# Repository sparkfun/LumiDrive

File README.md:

SparkFun LumiDrive LED Driver 
========================================

[*SparkFun LumiDrive LED Driver (14779)*](https://www.sparkfun.com/products/14779)

The LumiDrive LED Driver is SparkFun’s foray into all things Python on micro-controllers. With the SparkFun LumiDrive you will be able to control and personalize a whole strand of APA102s directly from the board itself. We’ve broken out a number of analog and digital pins from the on board SAMD21G-AU microcontroller to incorporate your own external buttons, switches, and other interfaces to interact with your addressable LED strip.

It feels like Arduino, but without the need to upload and compile code. Because the LumiDrive opens up like a USB drive on your computer when you plug it in and the code you write lives directly inside the drive it feels very much like an Arduino-device. The fact that you don’t need to upload and compile code makes it a great transitionary LED driver from your traditional Arduino!

The SparkFun LumiDrive has been equipped with a USB-C connector which is capable enough to supply up to 1.5 Amps from a 3.1 USB port, a LiPo connector and charge circuit for portable power, as well as two poke-home connectors to allow you to plug in wires without the need for solder.

Repository Contents
-------------------

* **/Buzzard Labels** - Silkscreen Libraries for Eagle Files
* **/Hardware** - Eagle design files (.brd, .sch)

Documentation
--------------
* **[Hookup Guide](https://learn.sparkfun.com/tutorials/lumidrive-hookup-guide)** - Basic hookup guide for the LumiDrive LED Driver.
* **[Example Code](https://github.com/sparkfun/SparkFun_LumiDrive_Example_Code)** - Example Code for the LumiDrive LED Driver.

License Information
-------------------

This product is _**open source**_! 

Please review the LICENSE.md file for license information. 

If you have any questions or concerns on licensing, please contact techsupport@sparkfun.com.

Distributed as-is; no warranty is given.

- Your friends at SparkFun.

_<COLLABORATION CREDIT>_

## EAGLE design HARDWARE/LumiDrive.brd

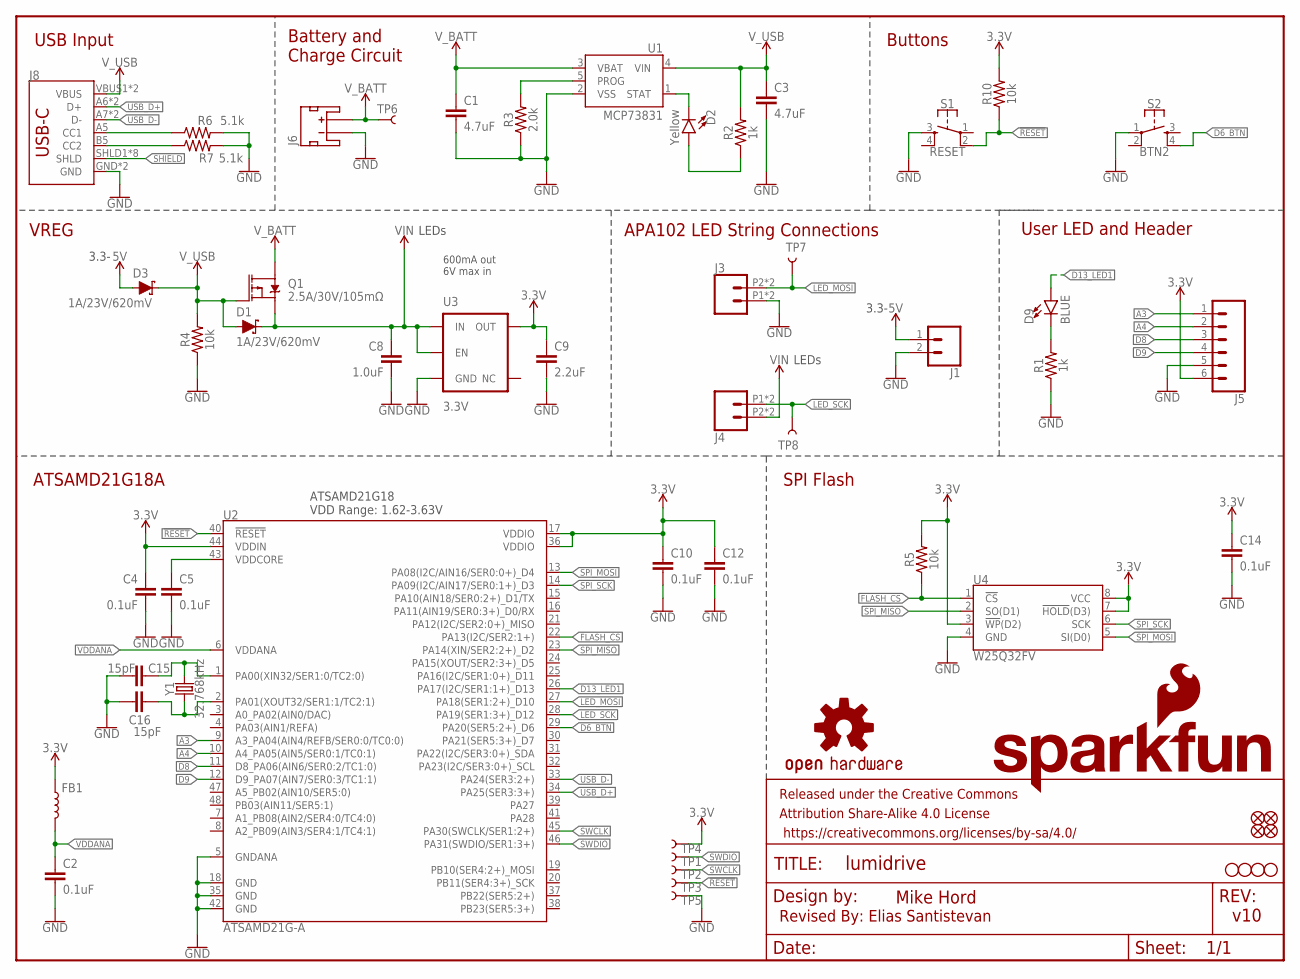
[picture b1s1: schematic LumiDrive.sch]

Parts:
C1, C3: 4.7uF; 0603
C2, C4, C5, C10, C12, C14: 0.1uF; 0603
C8: 1.0uF; 0805
C9: 2.2uF; 0603
C15, C16: 15pF; 0603
D1, D3: 1A/23V/620mV; SOD-323
D2: Yellow; LED-0603
D9: BLUE; LED-0603
FB1: 30Ω/1.8A; 0603
FD1, FD2, FD3, FD4: FIDUCIALUFIDUCIAL; FIDUCIAL-MICRO
FRAME1: FRAME-LETTER; CREATIVE_COMMONS
H1, H2, H3, H4: STAND-OFF
J1: CONN_021X02_NO_SILK; 1X02_NO_SILK
J3, J4: CONN_02SMALL_POKEHOME; 1X02_POKEHOME
J5: CONN_06NO_SILK_FEMALE_PTH; 1X06_NO_SILK
J6: JST_2MM_MALE; JST-2-SMD
J8: USB_C16PIN; USB-C-16P
LOGO1: OSHW-LOGOM; OSHW-LOGO-M
LOGO3: SFE_LOGO_NAME_FLAME.2_INCH; SFE_LOGO_NAME_FLAME_.2
Q1: 2.5A/30V/105mΩ; SOT23-3
R1, R2: 1k; 0603
R3: 2.0k; 0603
R4, R5, R10: 10k; 0603
R6, R7: 5.1k; 0603
S1: RESET; TACTILE_SWITCH_SMD_4.6X2.8MM
S2: BTN2; TACTILE_SWITCH_SMD_4.6X2.8MM
TP1: TP-SWDIO; PAD.03X.05
TP2: TP-SWCLK; PAD.03X.05
TP3: TP-!RESET!; PAD.03X.05
TP4: TP-3.3V; PAD.03X.05
TP5: TP-GND; PAD.03X.05
TP6, TP7, TP8: TEST-POINT3X4; PAD.03X.04
U1: MCP73831; SOT23-5
U2: ATSAMD21G-A; TQFP-48
U3: 3.3V; SOT23-5
U4: W25Q32FV; SOIC-8
Y1: 32.768kHz; CRYSTAL-SMD-3.2X1.5MM

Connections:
3.3V: C4.1, C9.1, C10.1, C12.1, C14.1, FB1.1, J5.6, R5.2, R10.2, TP4.P$1, U2.17 (VDDIO), U2.36 (VDDIO), U2.44 (VDDIN), U3.5 (OUT), U4.3 (!WP!(D2)), U4.7 (!HOLD!(D3)), U4.8 (VCC)
5V: D3.A, J1.1
!RESET: R10.1, S1.2, TP3.P$1, U2.40 (!RESET!)
A3: J5.1, U2.9 (A3_PA04(AIN4/REFB/SER0:0/TC0:0))
A4: J5.2, U2.10 (A4_PA05(AIN5/SER0:1/TC0:1))
D6_BTN: S2.4, U2.29 (PA20(SER5:2+)_D6)
D8: J5.3, U2.11 (D8_PA06(AIN6/SER0:2/TC1:0))
D9: J5.4, U2.12 (D9_PA07(AIN7/SER0:3/TC1:1))
D13_LED1: D9.A, U2.26 (PA17(I2C/SER1:1+)_D13)
FLASH_CS: R5.1, U2.22 (PA13(I2C/SER2:1+)), U4.1 (!CS!)
GND: C1.2, C2.2, C3.2, C4.2, C5.2, C8.2, C9.2, C10.2, C12.2, C14.2, C15.1, C16.1, J1.2, J3.P1 (1), J3.P3 (1), J5.5, J6.1 (-), J8.GND, J8.GND2 (GND), R1.1, R3.1, R4.1, R6.2, R7.2, S1.3, S2.1, TP5.P$1, U1.2 (VSS), U2.5 (GNDANA), U2.18 (GND), U2.35 (GND), U2.42 (GND), U3.2 (GND), U4.4 (GND)
LED_MOSI: J3.P2 (2), J3.P4 (2), TP7.P$1, U2.27 (PA18(SER1:2+)_D10)
LED_SCK: J4.P1 (1), J4.P3 (1), TP8.P$1, U2.28 (PA19(SER1:3+)_D12)
unnamed: D9.C, R1.2
unnamed: C15.2, U2.1 (PA00(XIN32/SER1:0/TC2:0)), Y1.P$2 (2)
unnamed: C16.2, U2.2 (PA01(XOUT32/SER1:1/TC2:1)), Y1.P$1 (1)
unnamed: D2.A, R2.1
unnamed: J8.B5 (CC2), R7.1
unnamed: J8.A5 (CC1), R6.1
unnamed: D2.C, U1.1 (STAT)
unnamed: R3.2, U1.5 (PROG)
SHIELD: J8.SHLD1 (SHLD), J8.SHLD2 (SHLD), J8.SHLD3 (SHLD), J8.SHLD4 (SHLD), J8.SHLD5 (SHLD), J8.SHLD6 (SHLD), J8.SHLD7 (SHLD), J8.SHLD8 (SHLD)
SPI_MISO: U2.23 (PA14(XIN/SER2:2+)_D2), U4.2 (SO(D1))
SPI_MOSI: U2.13 (PA08(I2C/AIN16/SER0:0+)_D4), U4.5 (SI(D0))
SPI_SCK: U2.14 (PA09(I2C/AIN17/SER0:1+)_D3), U4.6 (SCK)
SWCLK: TP2.P$1, U2.45 (PA30(SWCLK/SER1:2+))
SWDIO: TP1.P$1, U2.46 (PA31(SWDIO/SER1:3+))
USB_D+: J8.A6 (D+), J8.B6 (D+), U2.34 (PA25(SER3:3+))
USB_D-: J8.A7 (D-), J8.B7 (D-), U2.33 (PA24(SER3:2+))
VDDANA: C2.1, FB1.2, U2.6 (VDDANA)
VDDCORE: C5.1, U2.43 (VDDCORE)
VIN: C8.1, D1.C, J4.P2 (2), J4.P4 (2), Q1.2 (S), U3.1 (IN), U3.3 (EN)
V_BATT: C1.1, J6.2 (+), Q1.3 (D), TP6.P$1, U1.3 (VBAT)
V_USB: C3.1, D1.A, D3.C, J8.VBUS1 (VBUS), J8.VBUS2 (VBUS), Q1.1 (G), R2.2, R4.2, U1.4 (VIN)

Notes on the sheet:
600mA out 6V max in
v10
Mike Hord
ATSAMD21G18 VDD Range: 1.62-3.63V
USB Input
Buttons
SPI Flash
ATSAMD21G18A
User LED and Header
VREG
APA102 LED String Connections
Battery and Charge Circuit
Revised By: Elias Santistevan
3.3-
LEDs

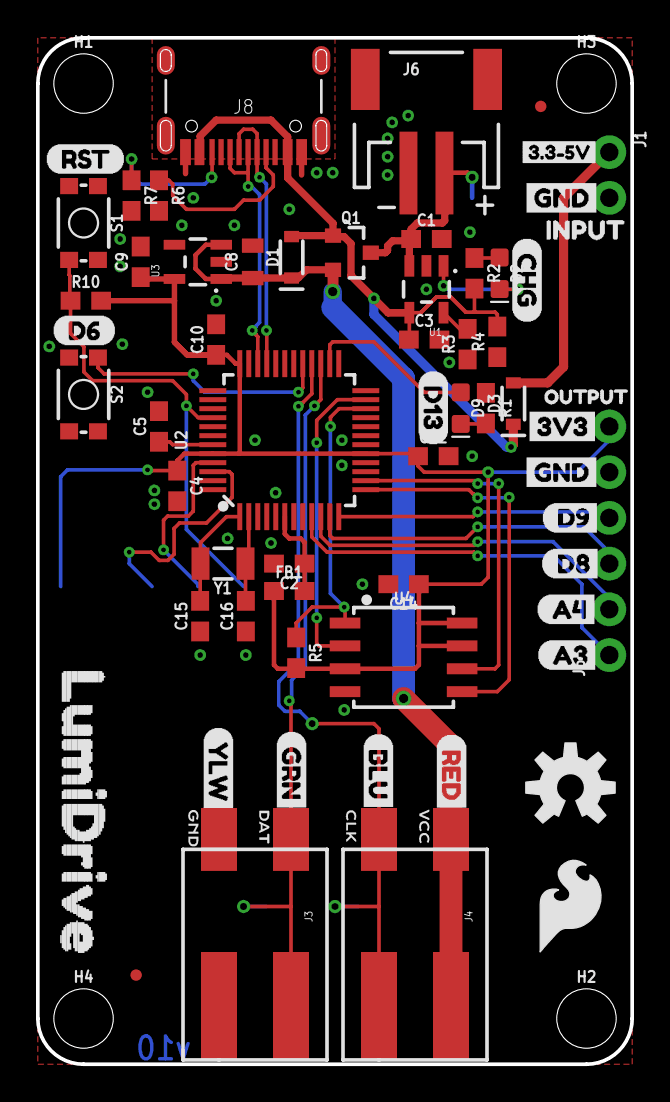
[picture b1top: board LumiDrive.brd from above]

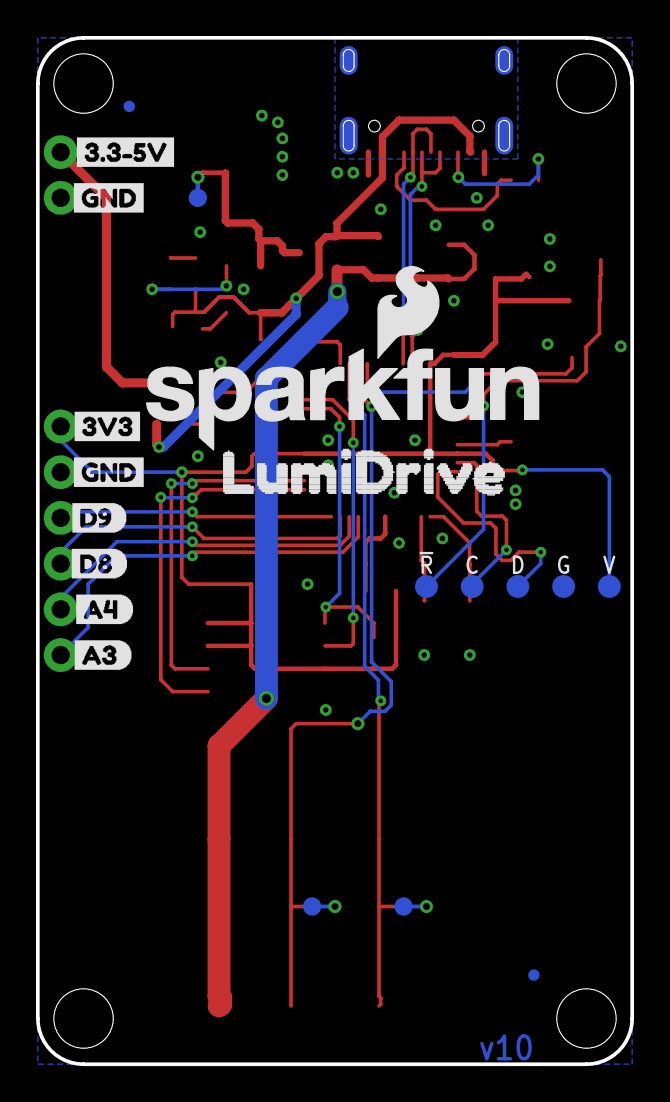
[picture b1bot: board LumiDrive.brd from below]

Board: 2 copper layers, 33.0 x 57.0 mm, 91 parts (20 on the bottom side), 34 nets.

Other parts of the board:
U$1, U$5, U$19, U$26: GND-04
U$2: GRN0
U$3: BLU0
U$4: YLW0
U$6, U$41: LUMIDRIVE0
U$8, U$29: 3#3#5V0
U$9: INPUT0
U$10: RED0
U$11: RST0
U$12: D60
U$13: CLK1
U$14: DAT2
U$15: GND0
U$16: VCC3
U$17: CHG0
U$18: D130
U$20, U$27: 3V3-04
U$21, U$40: D90
U$22, U$39: D80
U$23, U$38: A40
U$24, U$37: A30
U$25: OUTPUT0
U$28: SFE_LOGO_FLAME_.2

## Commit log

2018-11-02 Ready for protos round 2 (round 1 for me)
2018-11-02 Prototype Gerbers
2018-12-04 Adds production files and assembly sheet, and fixes swapped lipo connector pads
2018-12-04 Adds testpoints to LED SLCK and MOSI lines, extra silk labels for INPUT and OUTPUT .....
    labeling INPUT as 3.3V-5V, deletes old production files
2018-12-05 Adds clarifying text to the 5V and VIN power symbol, changes silk from "VIN" to "3.3V-5V" , and localizes the "OUTPUT" silk better
    - Changes DRC to tight with approval of the drill hit errors for better clarification on design choices
2018-12-06 Moves entire design down .005 mils to X-center
2019-02-01 Rename License.md to LICENSE.MD

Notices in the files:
parts and their libraries:
SparkFun-Resistors: Licensing: Creative Commons ShareAlike 4.0 International - https://creativecommons.org/licenses/by-sa/4.0
SparkFun-Aesthetics: Released under the Creative Commons Attribution Share-Alike 4.0 License
SparkFun-Aesthetics: https://creativecommons.org/licenses/by-sa/4.0
